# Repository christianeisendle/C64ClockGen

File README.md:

# C64 Clock Generator
## Introduction
This is a replacement for the MOS 8701 clock generator IC used in C64 board revisions 250425-01 and later.
It's not a 1:1 replica but the generated clocks follow more strictly the PAL specification.
MOS 8701 is a simple PLL which generates two clocks using a 17.734475 MHz XTAL oscillator. These clocks are:
- Color clock using directly the oscillator frequency of 17.734475 MHz
- Dot clock ("pixel clock") running at 7.8882 MHz

The Dot clock is generated by multiplying the color clock by 4 and divide by 9: 

$`\frac{17.734475MHz * 4}{9} = 7.8882MHz`$

Furthermore, VIC divides the dot clock by 8 (as one character consists of 8 pixel and memory access is character based) which gives the $`\phi0`$ clock of 0.986025MHz which is also the resulting CPU and VIC frequency. This is where C64 violates the PAL standard: One raster line is made of 63 CPU/VIC cycles which gives a duration of

$`\frac{1}{0.986025MHz}*63 = 63.8929us`$

However, PAL defines the horizontal/line frequency as 15.625kHz which is 64us. So C64 is off here by 

$`1-\frac{63.8929us}{64us} = 1.676\%`$

On old CRT screens this isn't really an issue as they make use of the synchronization pulses within the video signal. However, modern LCD screens (which perform internal AD conversion of the video signal) are quite strict on these tolerances and produce screen artifacts in case frequency deviation becomes too big. In particular, Samsung based models need an exact ratio between the color frequency of the video signal and the horizontal/vertical line/screen frequency as defined by PAL. While C64 precisely implements the color frequency of 4.43361875 MHz (which is the 17.734475 MHz color clock divided by 4) the line/screen frequency and with that the overall ratio is off.

## Design
{:width="400px"}
This clock generator uses a the IDT5V49EE902 programable clock generator from Renasas to generate the required clocks. This IC has a built-in EEPROM to store the configuration, i.e. an extra microcontroller is not needed for operation (but required for initial programming). The integrated XTAL oscillator uses the existing 17.734475 MHz XTAL on the C64 board, so only MOS 8701 needs to be replaced. The color clock is directly generated by this oscillator while the dot clock is created using frequency synthesis and the included PLL. The PLL output frequency is configured to 425.25 MHz which is fed into an output divider of ratio 54. The output frequency based on input frequency is defined as:

$`f_{out} = f_{in} * \frac{M}{D} * Q`$

where M and D are the PLL loop dividers and Q is the output divider. With M = 1127, D = 47 and Q = 54 we get the following dot clock for an input frequency of 17.734475 MHz:

$`f_{out} = 17.734475MHz * \frac{1127}{47} * 54 = 7.875MHz`$

This results in a line frequency of

$`f_{line} =  \frac{7.875MHz}{8} / 63 = 15.625kHz`$

## Programming the IDT5V49EE902
The python script in `pll/prog.py` contains the programming sequence for the IDT5V49EE902 using I2C. The script can be executed on a Raspberry Pi Pico running MicroPython (https://www.raspberrypi.com/documentation/microcontrollers/micropython.html). Porting it to another MicroController or a USB to I2C bridge should be easily possible. The C64 Clock Generator Board has two I2C testpads exposed with on board pull-up resistors.

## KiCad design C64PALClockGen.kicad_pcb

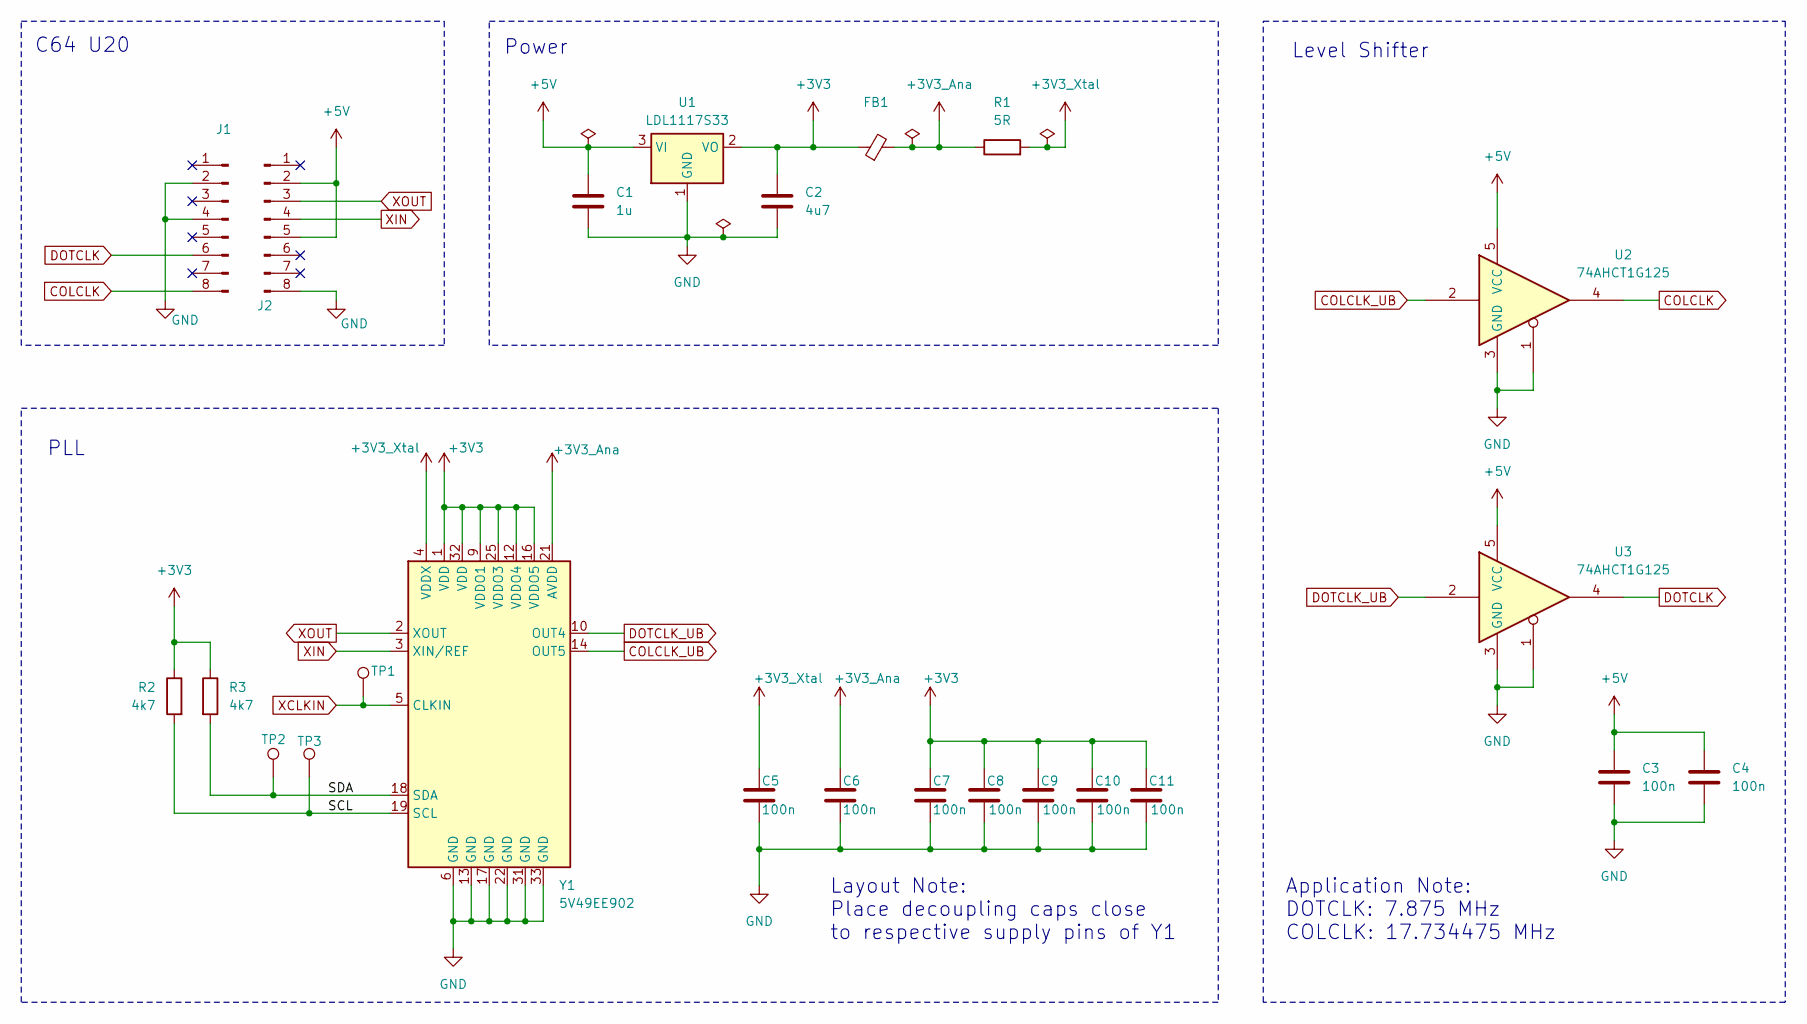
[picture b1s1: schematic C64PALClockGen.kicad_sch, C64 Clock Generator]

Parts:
C1: 1u; C_0603_1608Metric
C2: 4u7; C_0603_1608Metric
C3, C4, C5, C6, C7, C8, C9, C10, C11: 100n; R_0603_1608Metric_Pad0.98x0.95mm_HandSolder
FB1: FerriteBead_Small; R_0603_1608Metric_Pad0.98x0.95mm_HandSolder
J1, J2: Conn_01x08_Pin; PinHeader_1x08_P2.54mm_Vertical
R1: 5R; R_0603_1608Metric_Pad0.98x0.95mm_HandSolder
R2, R3: 4k7; R_0603_1608Metric_Pad0.98x0.95mm_HandSolder
TP1: CLKIN; TestPoint_Pad_D1.0mm
TP2: SDA; TestPoint_Pad_D1.0mm
TP3: SCL; TestPoint_Pad_D1.0mm
U1: LDL1117S33; SOT-223-3_TabPin2
U2, U3: 74AHCT1G125; SOT-353_SC-70-5
Y1: 5V49EE902; QFN-32-1EP_5x5mm_P0.5mm_EP3.3x3.3mm

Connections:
+3V3: C2.1, C7.1, C8.1, C9.1, C10.1, C11.1, FB1.1, R2.1, R3.1, U1.2 (VO), Y1.1 (VDD), Y1.9 (VDDO1), Y1.12 (VDDO4), Y1.16 (VDDO5), Y1.25 (VDDO3), Y1.32 (VDD)
+3V3_Ana: C6.1, FB1.2, R1.1, Y1.21 (AVDD)
+3V3_Xtal: C5.1, R1.2, Y1.4 (VDDX)
+5V: C1.1, C3.1, C4.1, J2.2, J2.5, U1.3 (VI), U2.5 (VCC), U3.5 (VCC)
/SCL: R2.2, TP3.1 (1_1), Y1.19 (SCL)
/SDA: R3.2, TP2.1 (1_1), Y1.18 (SDA)
COLCLK: J1.8, U2.4
COLCLK_UB: U2.2, Y1.14 (OUT5)
DOTCLK: J1.6, U3.4
DOTCLK_UB: U3.2, Y1.10 (OUT4)
GND: C1.2, C2.2, C3.2, C4.2, C5.2, C6.2, C7.2, C8.2, C9.2, C10.2, C11.2, J1.2, J1.4, J2.8, U1.1 (GND), U2.1, U2.3 (GND), U3.1, U3.3 (GND), Y1.6 (GND), Y1.13 (GND), Y1.17 (GND), Y1.22 (GND), Y1.31 (GND), Y1.33 (GND)
XCLKIN: TP1.1 (1_1), Y1.5 (CLKIN)
XIN: J2.4, Y1.3 (XIN/REF)
XOUT: J2.3, Y1.2 (XOUT)

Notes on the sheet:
C64 U20
Level Shifter
Layout Note: Place decoupling caps close to respective supply pins of Y1
Power
PLL
Application Note: DOTCLK: 7.875 MHz COLCLK: 17.734475 MHz

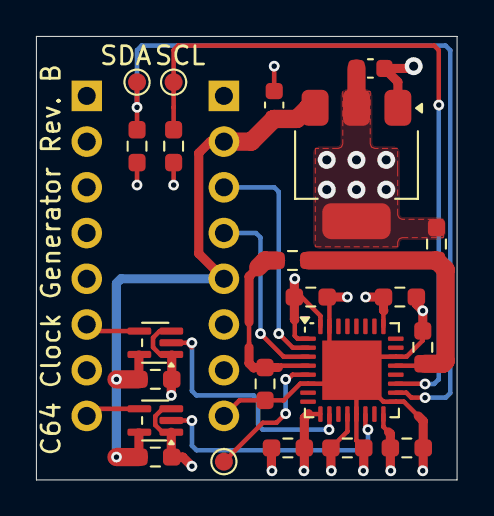
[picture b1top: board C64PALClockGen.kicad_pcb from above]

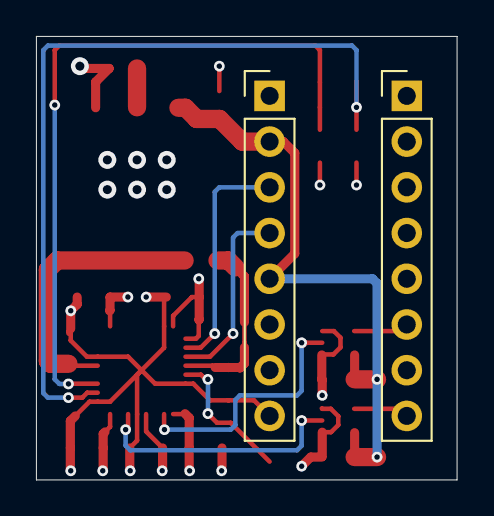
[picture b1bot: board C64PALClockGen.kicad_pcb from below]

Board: 4 copper layers, 23.4 x 24.6 mm, 24 parts (2 on the bottom side), 14 nets.

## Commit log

2026-04-09 Finalized v2 dual layer
2026-04-14 C64 Clock Generator Rev.B
2026-04-14 Remove layout pdfs
2026-04-14 Remove legacy file
2026-04-14 Re-generated schematic.pdf
2026-04-14 Create LICENSE
2026-04-15 Add README.md
2026-04-23 Rework programming script
    - Use mod_reg and set/clear bit helpers to avoid accidental overwrite of values
    - Add more documentation
